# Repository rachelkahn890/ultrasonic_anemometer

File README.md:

# ultrasonic_anemometer
Development of a low-cost ultrasonic anemometer. Still in progress, please excuse my poor file labeling techniques.

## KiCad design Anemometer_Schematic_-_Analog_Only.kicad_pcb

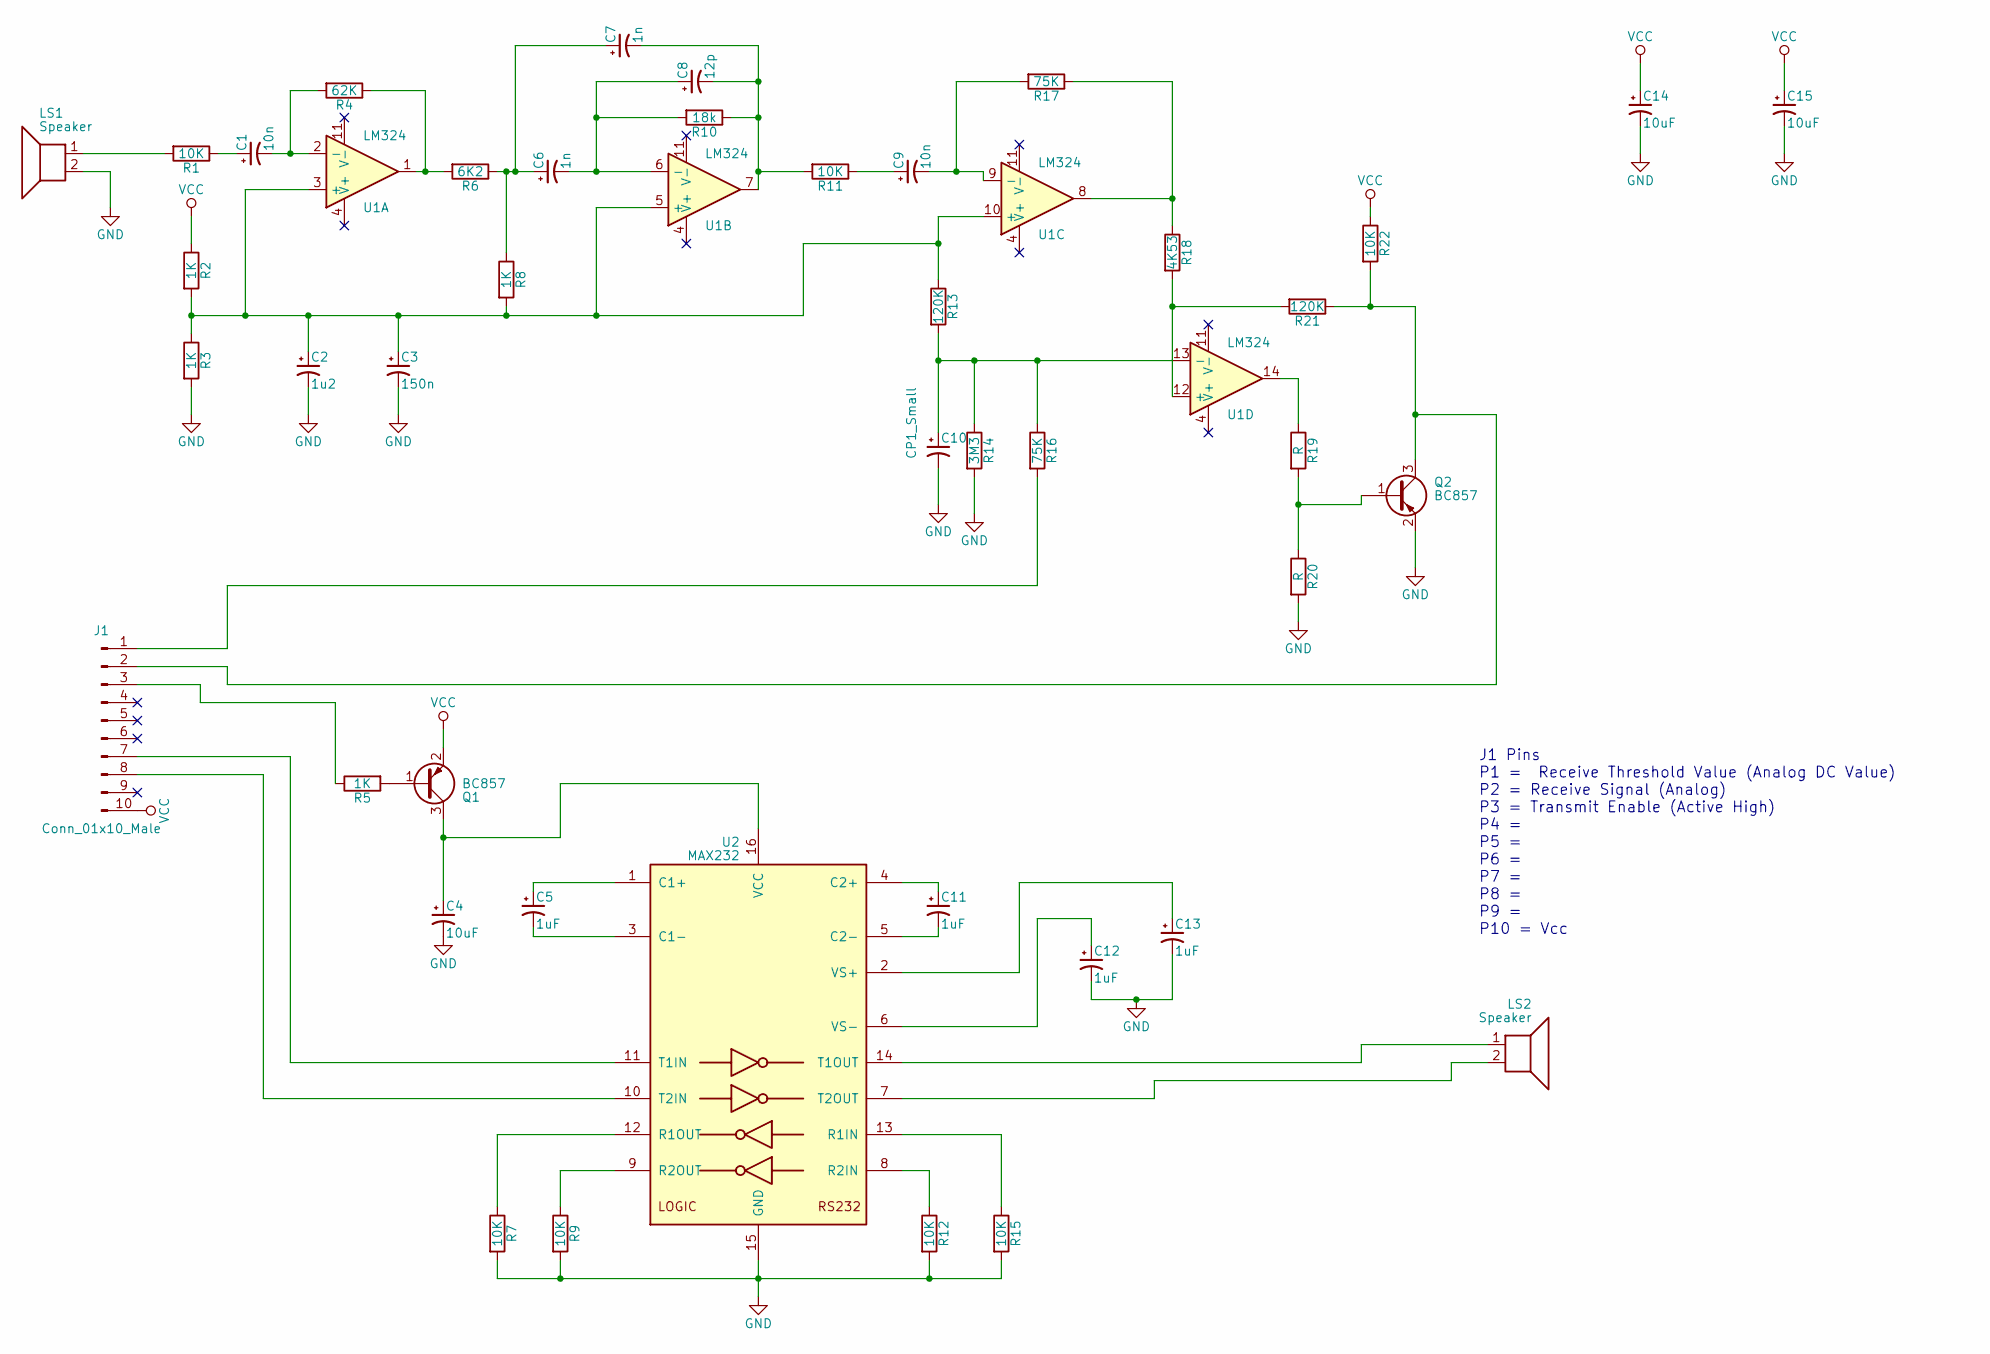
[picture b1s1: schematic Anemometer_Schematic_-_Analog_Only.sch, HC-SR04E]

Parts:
C1, C9: 10n; C_0603_HandSoldering
C2: 1u2; C_0603_HandSoldering
C3: 150n; C_0603_HandSoldering
C4, C14, C15: 10uF; C_0603_HandSoldering
C5, C11, C12, C13: 1uF; C_0603_HandSoldering
C6, C7: 1n; C_0603_HandSoldering
C8: 12p; C_0603_HandSoldering
C10: CP1_Small; C_0603_HandSoldering
J1: Conn_01x10_Male; Socket_Strip_Straight_1x10_Pitch2.54mm
LS1, LS2: Speaker; ultrasonic_speaker
Q1, Q2: BC857; SOT-23
R1, R7, R9, R11, R12, R15, R22: 10K; R_0603_HandSoldering
R2, R3, R5, R8: 1K; R_0603_HandSoldering
R4: 62K; R_0603_HandSoldering
R6: 6K2; R_0603_HandSoldering
R10: 18k; R_0603_HandSoldering
R13, R21: 120K; R_0603_HandSoldering
R14: 3M3; R_0603_HandSoldering
R16, R17: 75K; R_0603_HandSoldering
R18: 4K53; R_0603_HandSoldering
R19, R20: R; R_0603_HandSoldering
U1: LM324
U2: MAX232; MAX232A

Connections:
GND: C2.2, C3.2, C4.2, C10.2, C12.2, C13.2, C14.2, C15.2, LS1.2, Q2.2 (E), R3.2, R7.2, R9.2, R12.2, R14.2, R15.2, R20.2, U2.15 (GND)
unnamed: C1.1, R1.1
unnamed: C1.2, R4.2, U1.2 (-)
unnamed: C2.1, C3.1, R2.2, R3.1, R8.2, R13.1, U1.3 (+), U1.5 (+), U1.10 (+)
unnamed: C4.1, Q1.3 (C), U2.16 (VCC)
unnamed: C5.1, U2.1 (C1+)
unnamed: C5.2, U2.3 (C1-)
unnamed: C6.1, C7.1, R6.1, R8.1
unnamed: C6.2, C8.1, R10.2, U1.6 (-)
unnamed: C7.2, C8.2, R10.1, R11.2, U1.7
unnamed: C9.1, R11.1
unnamed: C9.2, R17.2, U1.9 (-)
unnamed: C10.1, R13.2, R14.1, R16.1, U1.13 (-)
unnamed: C11.1, U2.4 (C2+)
unnamed: C11.2, U2.5 (C2-)
unnamed: C12.1, U2.6 (VS-)
unnamed: C13.1, U2.2 (VS+)
unnamed: J1.1, R16.2
unnamed: J1.2, Q2.3 (C), R21.1, R22.2
unnamed: J1.3, R5.1
unnamed: J1.7, U2.11 (T1IN)
unnamed: J1.8, U2.10 (T2IN)
unnamed: LS1.1, R1.2
unnamed: LS2.1, U2.14 (T1OUT)
unnamed: LS2.2, U2.7 (T2OUT)
unnamed: Q1.1 (B), R5.2
unnamed: Q2.1 (B), R19.2, R20.1
unnamed: R4.1, R6.2, U1.1
unnamed: R7.1, U2.12 (R1OUT)
unnamed: R9.1, U2.9 (R2OUT)
unnamed: R12.1, U2.8 (R2IN)
unnamed: R15.1, U2.13 (R1IN)
unnamed: R17.1, R18.1, U1.8
unnamed: R18.2, R21.2, U1.12 (+)
unnamed: R19.1, U1.14
VCC: C14.1, C15.1, J1.10, Q1.2 (E), R2.1, R22.1

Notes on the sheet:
J1 Pins P1 = Receive Threshold Value (Analog DC Value) P2 = Receive Signal (Analog) P3 = Transmit Enable (Active High) P4 = P5 = P6 = P7 = P8 = P9 = P10 = Vcc

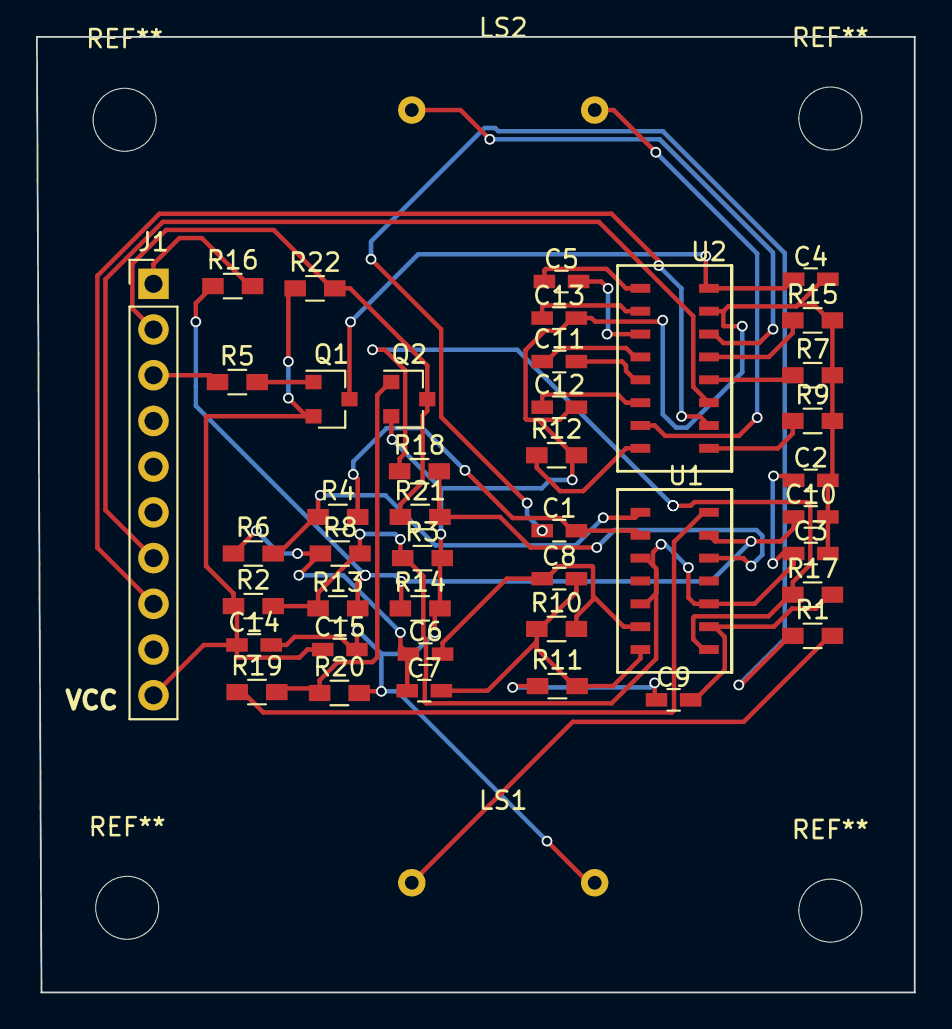
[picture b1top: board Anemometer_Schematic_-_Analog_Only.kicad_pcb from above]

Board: 2 copper layers, 48.8 x 53.1 mm, 44 parts (0 on the bottom side), 36 nets.

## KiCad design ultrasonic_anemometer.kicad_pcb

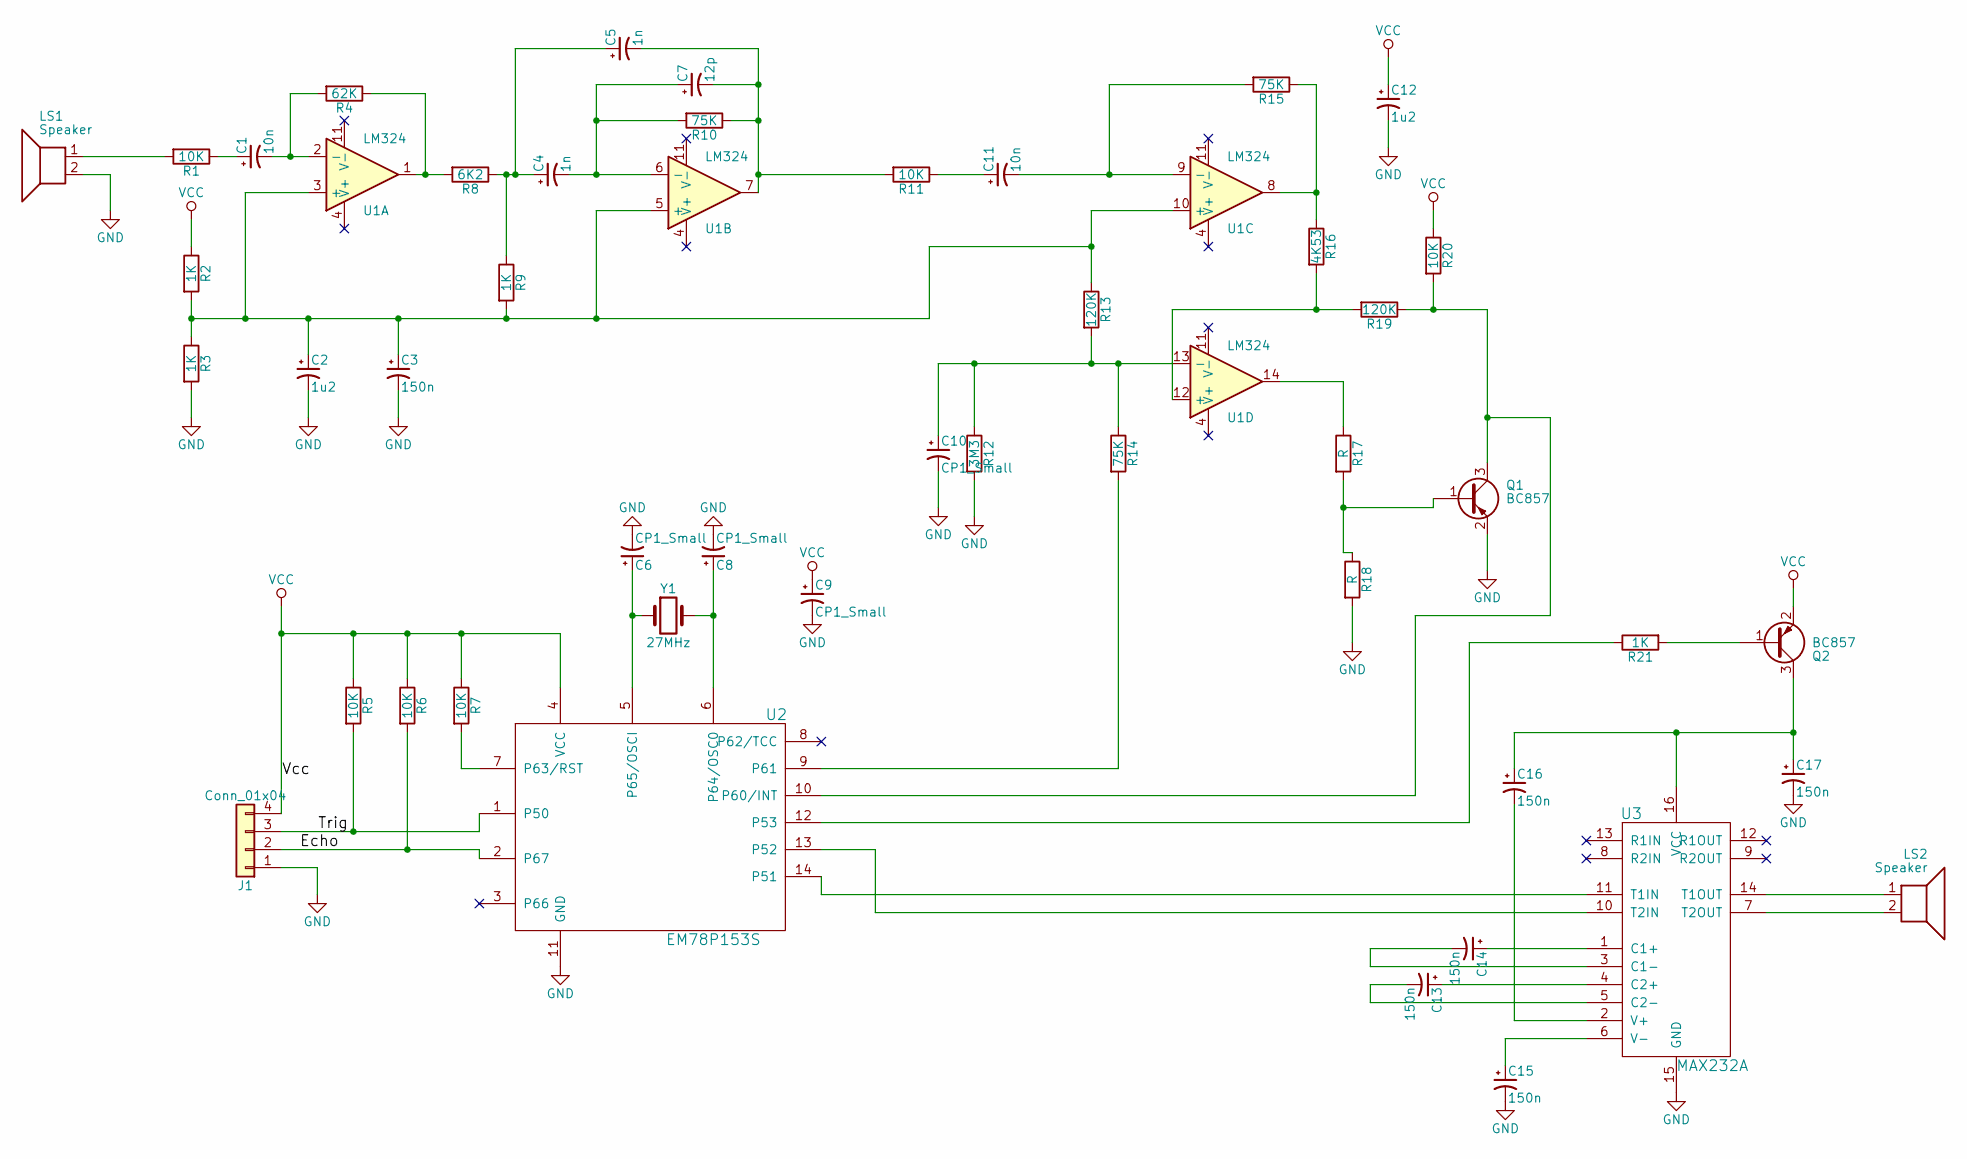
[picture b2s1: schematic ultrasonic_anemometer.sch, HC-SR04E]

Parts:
C1, C11: 10n; C_0603_HandSoldering
C2, C12: 1u2; C_0603_HandSoldering
C3, C13, C14, C15, C16, C17: 150n; C_0603_HandSoldering
C4, C5: 1n; C_0603_HandSoldering
C6, C8, C9, C10: CP1_Small; C_0603_HandSoldering
C7: 12p; C_0603_HandSoldering
J1: Conn_01x04; Socket_Strip_Straight_1x04_Pitch2.54mm
LS1, LS2: Speaker; ultrasonic_speaker
Q1, Q2: BC857; SOT-23
R1, R5, R6, R7, R11, R20: 10K; R_0603_HandSoldering
R2, R3, R9, R21: 1K; R_0603_HandSoldering
R4: 62K; R_0603_HandSoldering
R8: 6K2; R_0603_HandSoldering
R10, R14, R15: 75K; R_0603_HandSoldering
R12: 3M3; R_0603_HandSoldering
R13, R19: 120K; R_0603_HandSoldering
R16: 4K53; R_0603_HandSoldering
R17, R18: R; R_0603_HandSoldering
U1: LM324
U2: EM78P153S; EM78P153S_microcontroller
U3: MAX232A
Y1: 27MHz; HCSR04_crystal

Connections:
/Echo: J1.2, R6.2, U2.2 (P67)
/Trig: J1.3, R5.2, U2.1 (P50)
GND: C2.2, C3.2, C6.2, C8.2, C9.2, C10.2, C12.2, C15.2, C17.2, J1.1, LS1.2, Q1.2 (E), R3.2, R12.2, R18.2, U2.11 (GND), U3.15 (GND)
unnamed: C1.1, R1.1
unnamed: C1.2, R4.2, U1.2 (-)
unnamed: C2.1, C3.1, R2.2, R3.1, R9.2, R13.1, U1.3 (+), U1.5 (+), U1.10 (+)
unnamed: C4.1, C5.1, R8.1, R9.1
unnamed: C4.2, C7.1, R10.2, U1.6 (-)
unnamed: C5.2, C7.2, R10.1, R11.2, U1.7
unnamed: C6.1, U2.5 (P65/OSCI), Y1.1
unnamed: C8.1, U2.6 (P64/OSC0), Y1.2
unnamed: C10.1, R12.1, R13.2, R14.1, U1.13 (-)
unnamed: C11.1, R11.1
unnamed: C11.2, R15.2, U1.9 (-)
unnamed: C13.1, U3.4 (C2+)
unnamed: C13.2, U3.5 (C2-)
unnamed: C14.1, U3.1 (C1+)
unnamed: C14.2, U3.3 (C1-)
unnamed: C15.1, U3.6 (V-)
unnamed: C16.1, C17.1, Q2.3 (C), U3.16 (VCC)
unnamed: C16.2, U3.2 (V+)
unnamed: LS1.1, R1.2
unnamed: LS2.1, U3.14 (T1OUT)
unnamed: LS2.2, U3.7 (T2OUT)
unnamed: Q1.1 (B), R17.2, R18.1
unnamed: Q1.3 (C), R19.1, R20.2, U2.10 (P60/INT)
unnamed: Q2.1 (B), R21.2
unnamed: R4.1, R8.2, U1.1
unnamed: R7.2, U2.7 (P63/RST)
unnamed: R14.2, U2.9 (P61)
unnamed: R15.1, R16.1, U1.8
unnamed: R16.2, R19.2, U1.12 (+)
unnamed: R17.1, U1.14
unnamed: R21.1, U2.12 (P53)
unnamed: U2.13 (P52), U3.10 (T2IN)
unnamed: U2.14 (P51), U3.11 (T1IN)
VCC: C9.1, C12.1, J1.4, Q2.2 (E), R2.1, R5.1, R6.1, R7.1, R20.1, U2.4 (VCC)

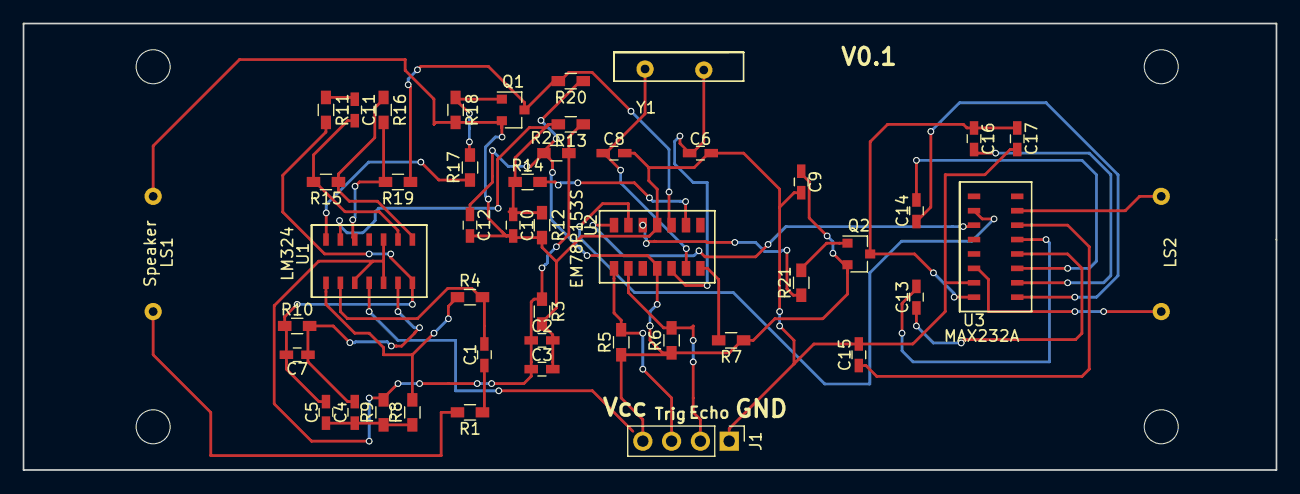
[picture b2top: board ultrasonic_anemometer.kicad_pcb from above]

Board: 2 copper layers, 110.5 x 39.4 mm, 47 parts (0 on the bottom side), 37 nets.

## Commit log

2017-10-17 Adding gerber and drill files
2017-10-17 Adding kicad files
2017-10-17 Updated gerber and drill files
2017-10-17 Updated kicad files
2017-10-17 Actual updated kicad files
    (forgot to save my project before committing)
2017-12-21 updated PCB files with labeled connector
